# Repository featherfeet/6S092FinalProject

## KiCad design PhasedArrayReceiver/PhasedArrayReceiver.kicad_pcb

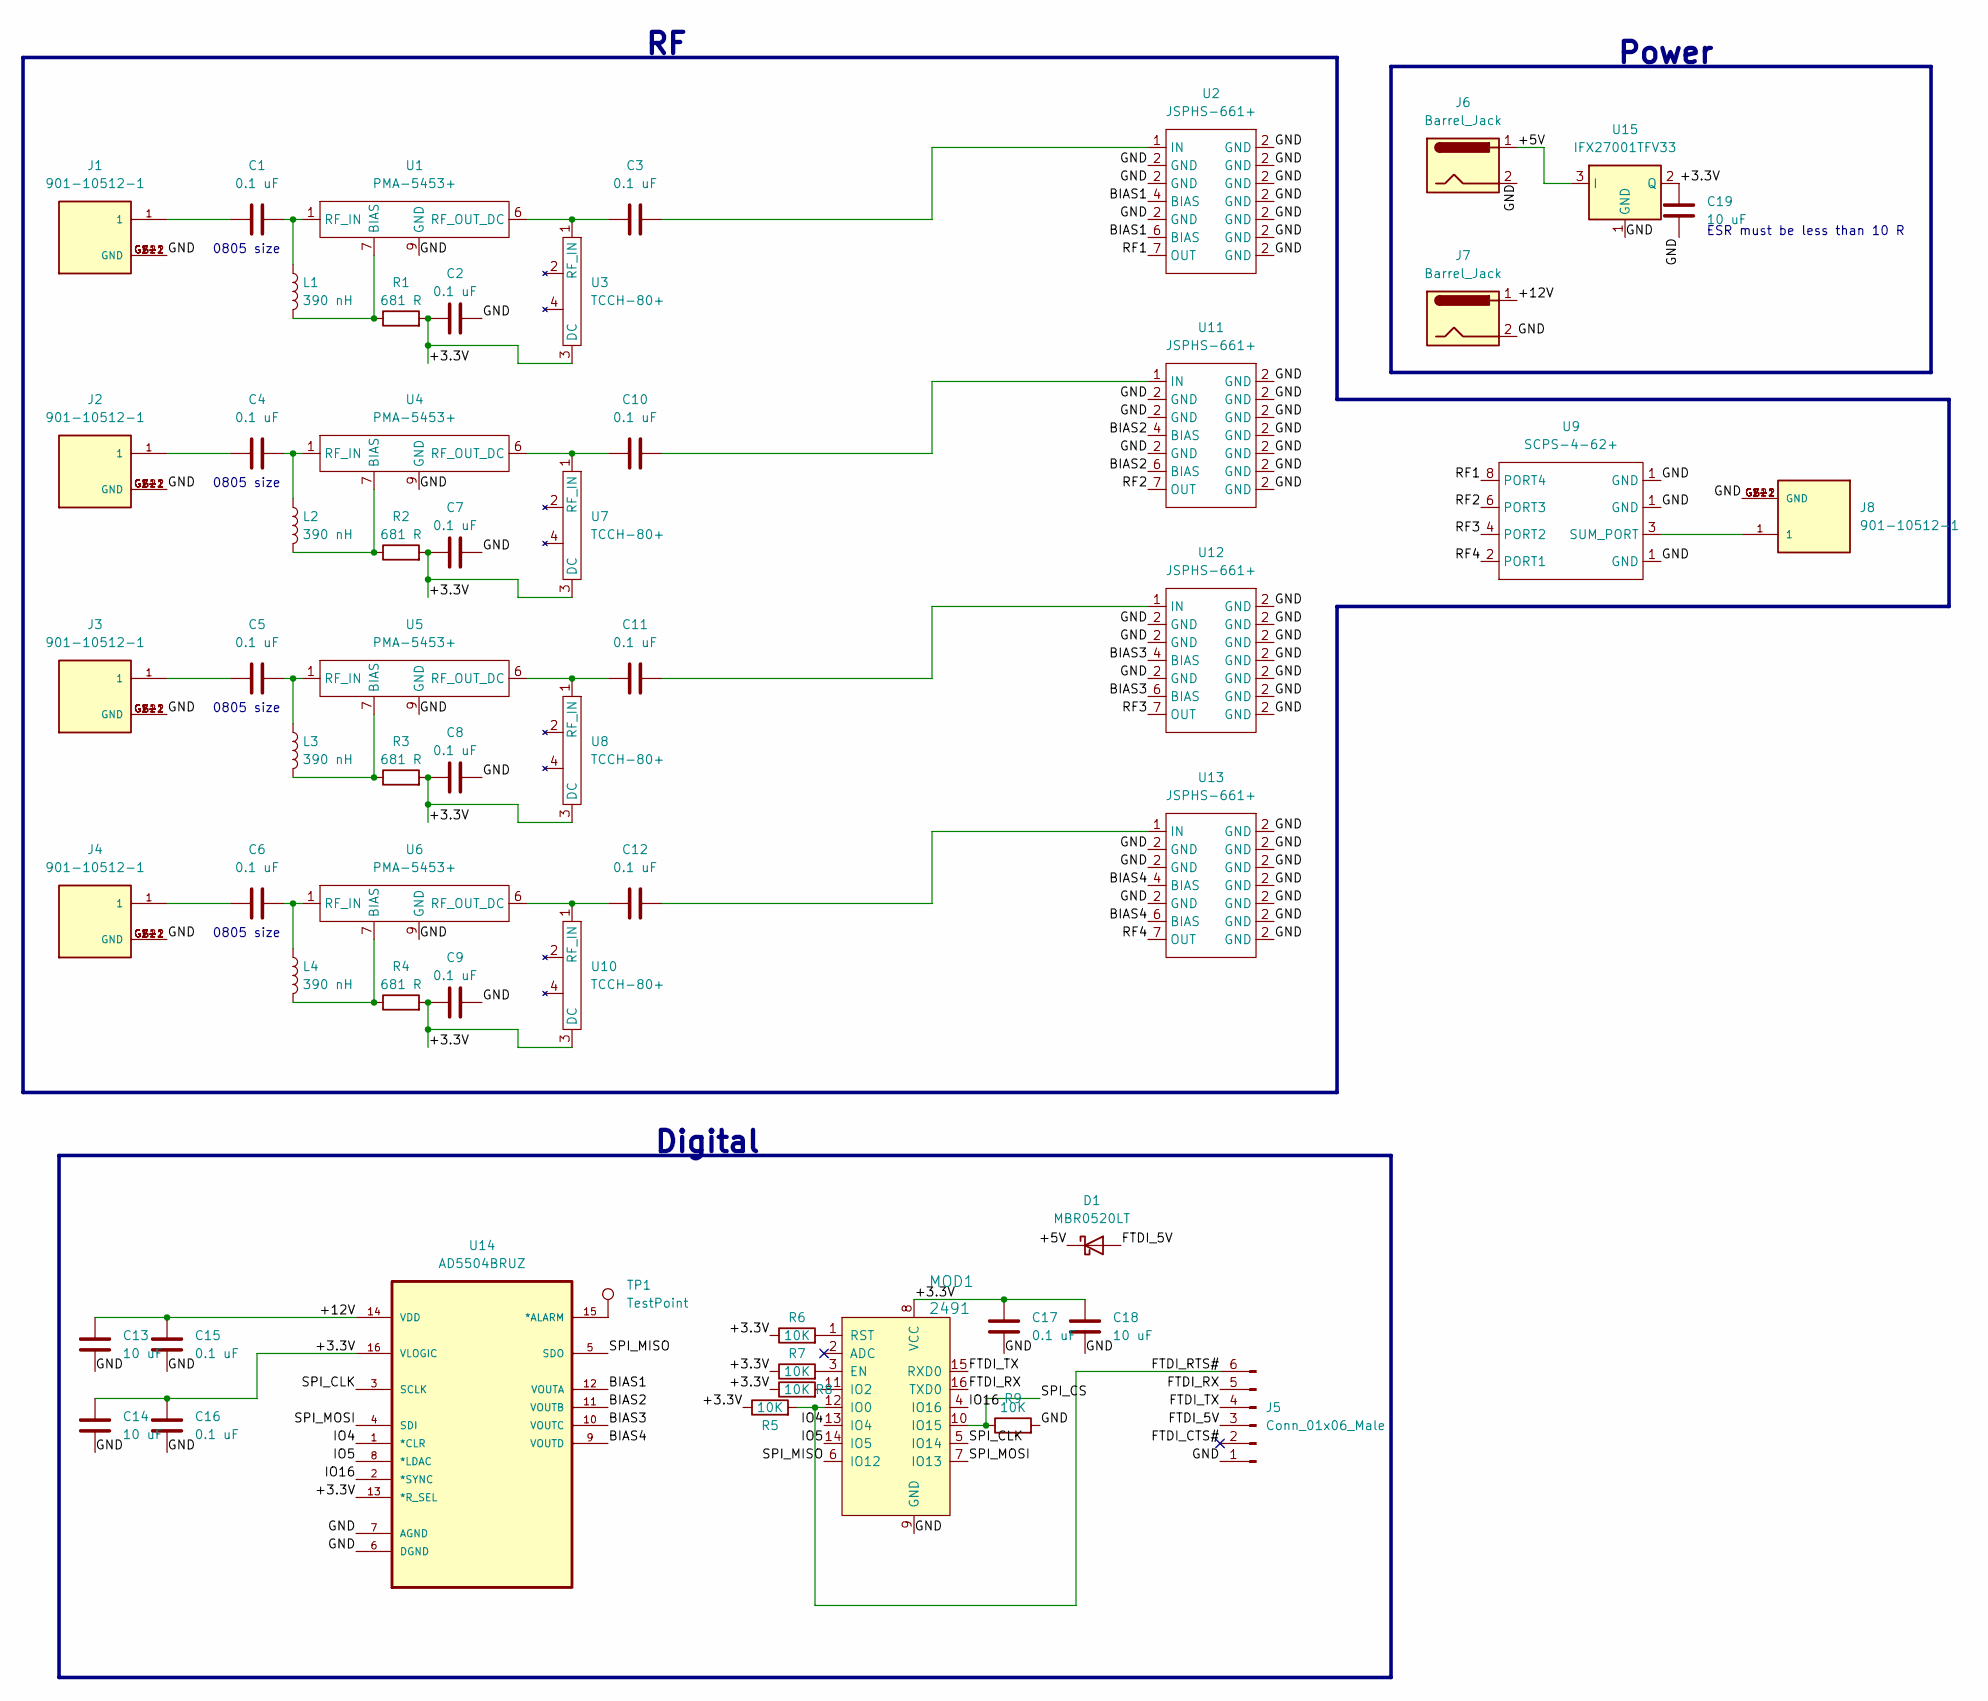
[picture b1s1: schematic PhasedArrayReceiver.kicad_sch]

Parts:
C1, C2, C3, C4, C5, C6, C7, C8, C9, C10, C11, C12, C15, C16, C17: 0.1 uF; CAPC2012X94N
C13, C14, C18, C19: 10 uF; CAPC2012X140N
D1: MBR0520LT; D_SOD-123
J1, J2, J3, J4, J8: 901-10512-1; AMPHENOL_901-10512-1; PARTREV A
J5: Conn_01x06_Male; PinHeader_1x06_P2.54mm_Vertical
J6, J7: Barrel_Jack; Barrel_Jack_5.5mmODx2.1mmID_PJ-202A
L1, L2, L3, L4: 390 nH; IND_AISC-0805-R39J-T
MOD1: 2491; WIFI_Module_ESP8266_2491; MPN 2491; Digi-Key_PN 1528-1438-ND
R1, R2, R3, R4: 681 R; RESC2012X60N
R5, R6, R7, R8, R9: 10K; RESC2012X65N
TP1: TestPoint; TestPoint_THTPad_1.0x1.0mm_Drill0.5mm
U1, U4, U5, U6: PMA-5453+
U2, U11, U12, U13: JSPHS-661+
U3, U7, U8, U10: TCCH-80+
U9: SCPS-4-62+
U14: AD5504BRUZ; SOP65P640X120-16N; MPN AD5504BRUZ
U15: IFX27001TFV33; TO-252-3_TabPin2

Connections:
/+3.3V: C2.1, C7.1, C8.1, C9.1, C14.1, C16.1, C17.1, C18.1, C19.1, MOD1.8 (VCC), R1.2, R2.2, R3.2, R4.2, R5.1, R6.1, R7.1, R8.1, U3.3 (DC), U7.3 (DC), U8.3 (DC), U10.3 (DC), U14.13 (*R_SEL), U14.16 (VLOGIC), U15.2 (Q)
/+5V: D1.1 (K), J6.1, U15.3 (I)
/+12V: C13.1, C15.1, J7.1, U14.14 (VDD)
/BIAS1: U2.4 (BIAS), U2.6 (BIAS), U14.12 (VOUTA)
/BIAS2: U11.4 (BIAS), U11.6 (BIAS), U14.11 (VOUTB)
/BIAS3: U12.4 (BIAS), U12.6 (BIAS), U14.10 (VOUTC)
/BIAS4: U13.4 (BIAS), U13.6 (BIAS), U14.9 (VOUTD)
/FTDI_5V: D1.2 (A), J5.3
/FTDI_CTS#: J5.2
/FTDI_RTS#: J5.6, MOD1.12 (IO0), R5.2
/FTDI_RX: J5.5, MOD1.16 (TXD0)
/FTDI_TX: J5.4, MOD1.15 (RXD0)
/GND: C2.2, C7.2, C8.2, C9.2, C13.2, C14.2, C15.2, C16.2, C17.2, C18.2, C19.2, J1.G1 (GND), J1.G1-1 (GND), J1.G1-2 (GND), J1.G2 (GND), J1.G2-1 (GND), J1.G2-2 (GND), J2.G1 (GND), J2.G1-1 (GND), J2.G1-2 (GND), J2.G2 (GND), J2.G2-1 (GND), J2.G2-2 (GND), J3.G1 (GND), J3.G1-1 (GND), J3.G1-2 (GND), J3.G2 (GND), J3.G2-1 (GND), J3.G2-2 (GND), J4.G1 (GND), J4.G1-1 (GND), J4.G1-2 (GND), J4.G2 (GND), J4.G2-1 (GND), J4.G2-2 (GND), J5.1, J6.2, J7.2, J8.G1 (GND), J8.G1-1 (GND), J8.G1-2 (GND), J8.G2 (GND), J8.G2-1 (GND), J8.G2-2 (GND), MOD1.9 (GND), R9.2, U1.9 (GND), U2.2 (GND), U4.9 (GND), U5.9 (GND), U6.9 (GND), U9.1 (GND), U11.2 (GND), U12.2 (GND), U13.2 (GND), U14.6 (DGND), U14.7 (AGND), U15.1 (GND)
/IO4: MOD1.13 (IO4), U14.1 (*CLR)
/IO5: MOD1.14 (IO5), U14.8 (*LDAC)
/IO16: MOD1.4 (IO16), U14.2 (*SYNC)
/RF1: U2.7 (OUT), U9.8 (PORT4)
/RF2: U9.6 (PORT3), U11.7 (OUT)
/RF3: U9.4 (PORT2), U12.7 (OUT)
/RF4: U9.2 (PORT1), U13.7 (OUT)
/SPI_CLK: MOD1.5 (IO14), U14.3 (SCLK)
/SPI_CS: MOD1.10 (IO15), R9.1
/SPI_MISO: MOD1.6 (IO12), U14.5 (SDO)
/SPI_MOSI: MOD1.7 (IO13), U14.4 (SDI)
unnamed: C1.1, J1.1
unnamed: C1.2, L1.1, U1.1 (RF_IN)
unnamed: C3.1, U1.6 (RF_OUT_DC), U3.1 (RF_IN)
unnamed: C3.2, U2.1 (IN)
unnamed: C4.1, J2.1
unnamed: C4.2, L2.1, U4.1 (RF_IN)
unnamed: C5.1, J3.1
unnamed: C5.2, L3.1, U5.1 (RF_IN)
unnamed: C6.1, J4.1
unnamed: C6.2, L4.1, U6.1 (RF_IN)
unnamed: C10.1, U4.6 (RF_OUT_DC), U7.1 (RF_IN)
unnamed: C10.2, U11.1 (IN)
unnamed: C11.1, U5.6 (RF_OUT_DC), U8.1 (RF_IN)
unnamed: C11.2, U12.1 (IN)
unnamed: C12.1, U6.6 (RF_OUT_DC), U10.1 (RF_IN)
unnamed: C12.2, U13.1 (IN)
unnamed: J8.1, U9.3 (SUM_PORT)
unnamed: L1.2, R1.1, U1.7 (BIAS)
unnamed: L2.2, R2.1, U4.7 (BIAS)
unnamed: L3.2, R3.1, U5.7 (BIAS)
unnamed: L4.2, R4.1, U6.7 (BIAS)
unnamed: MOD1.1 (RST), R6.2
unnamed: MOD1.3 (EN), R7.2
unnamed: MOD1.11 (IO2), R8.2
unnamed: TP1.1, U14.15 (*ALARM)

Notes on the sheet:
0805 size
ESR must be less than 10 R
Power
Digital

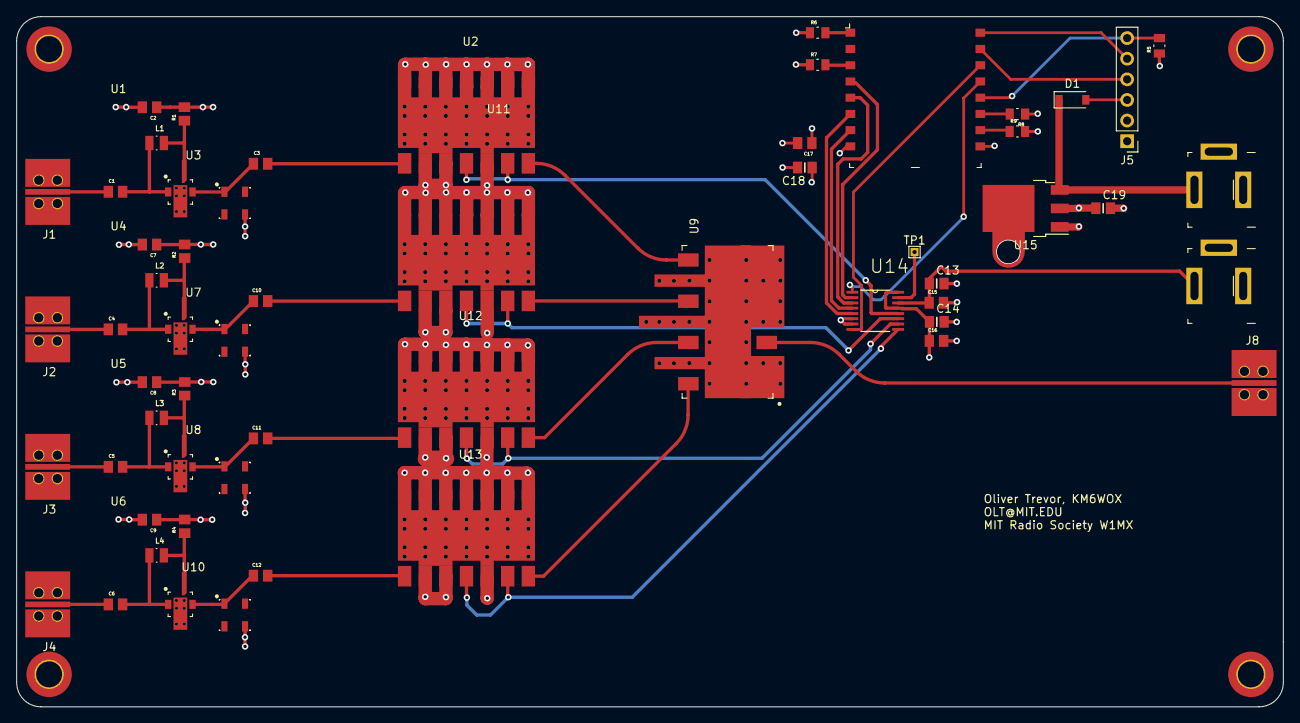
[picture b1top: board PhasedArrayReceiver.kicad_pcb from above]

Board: 4 copper layers, 156.0 x 85.0 mm, 58 parts (0 on the bottom side), 48 nets.

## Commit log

2023-02-03 Done!
